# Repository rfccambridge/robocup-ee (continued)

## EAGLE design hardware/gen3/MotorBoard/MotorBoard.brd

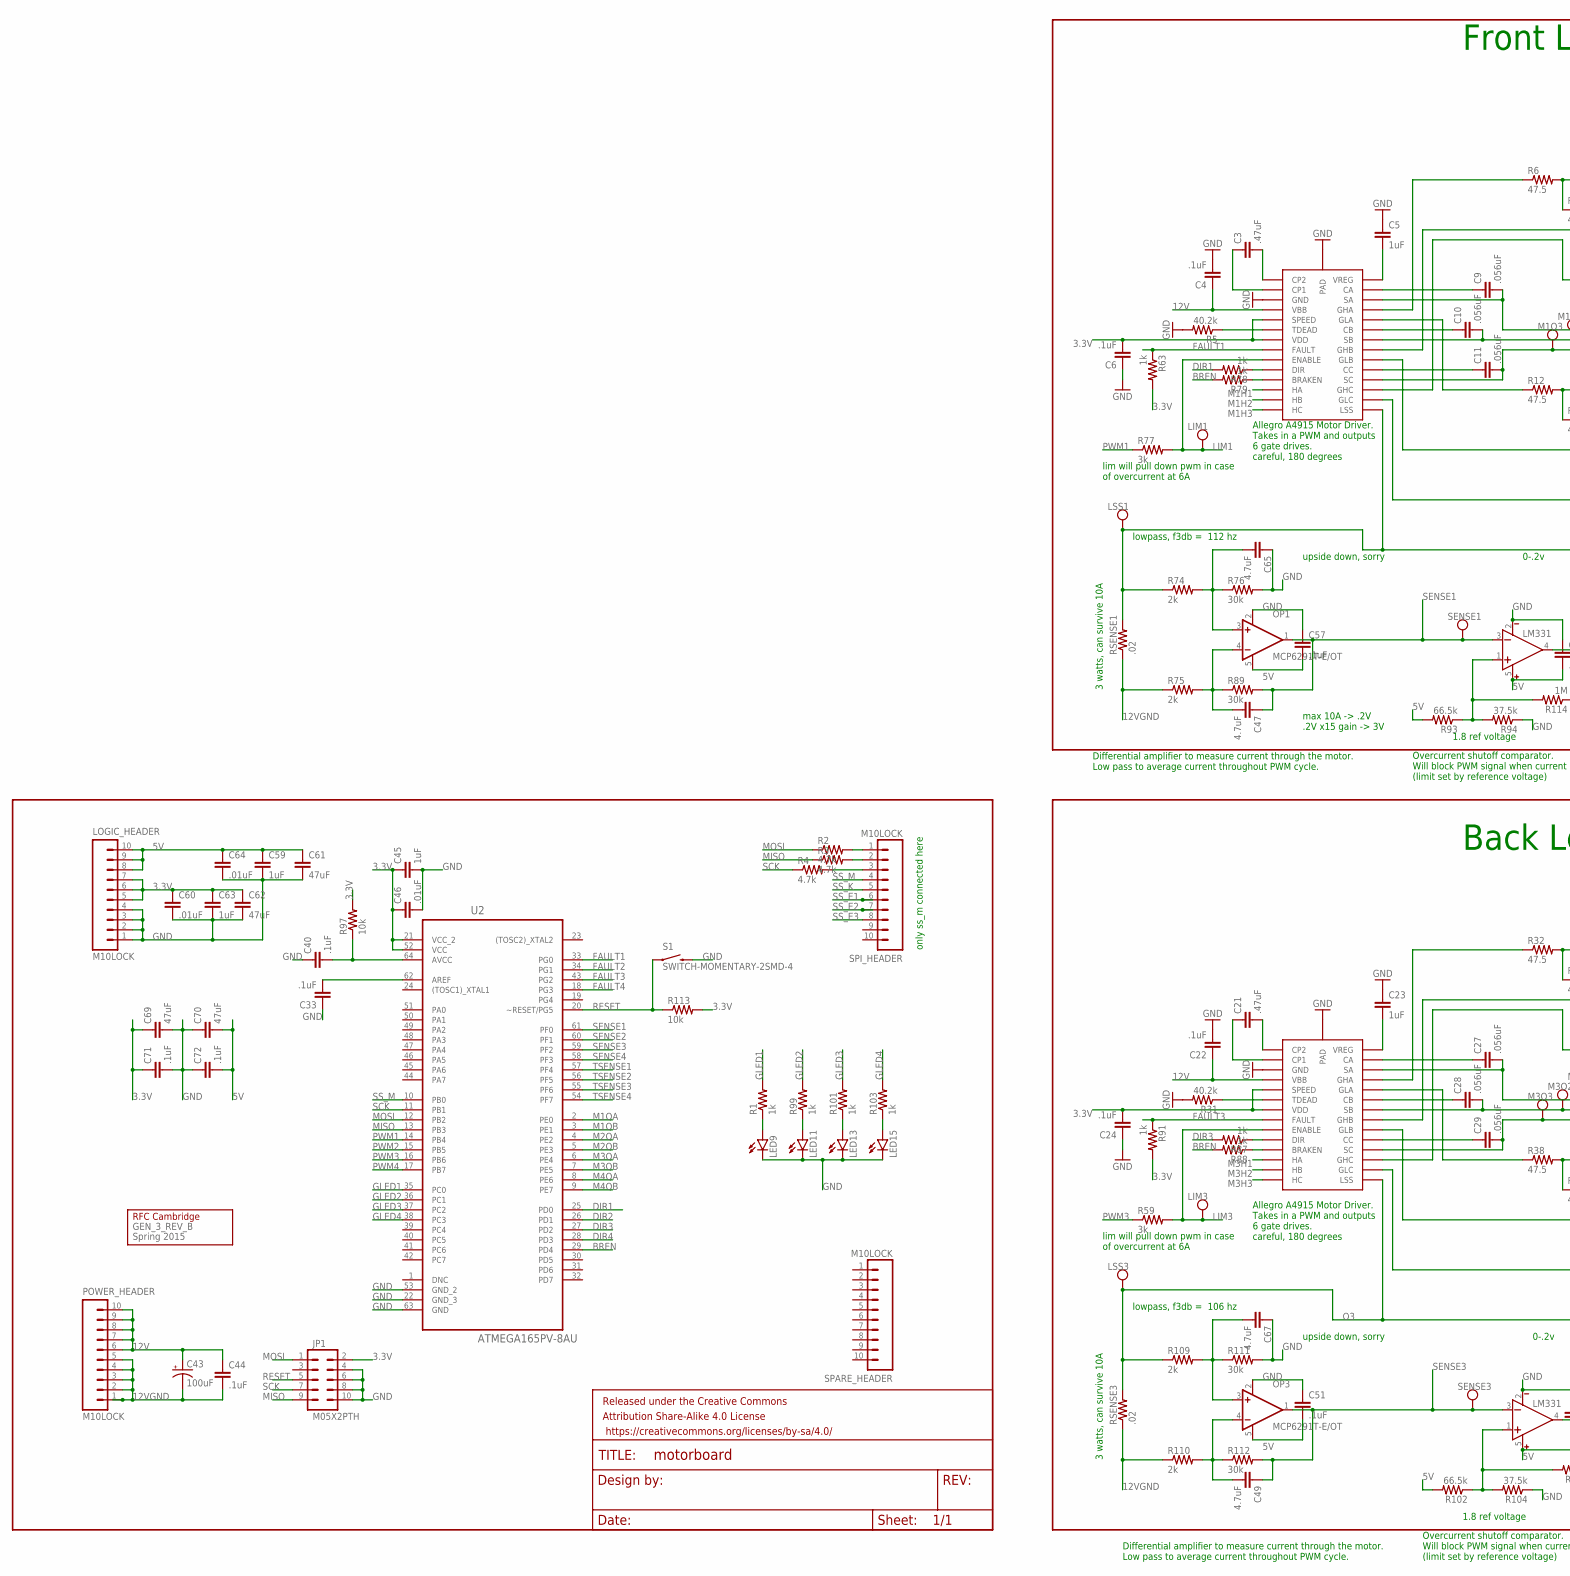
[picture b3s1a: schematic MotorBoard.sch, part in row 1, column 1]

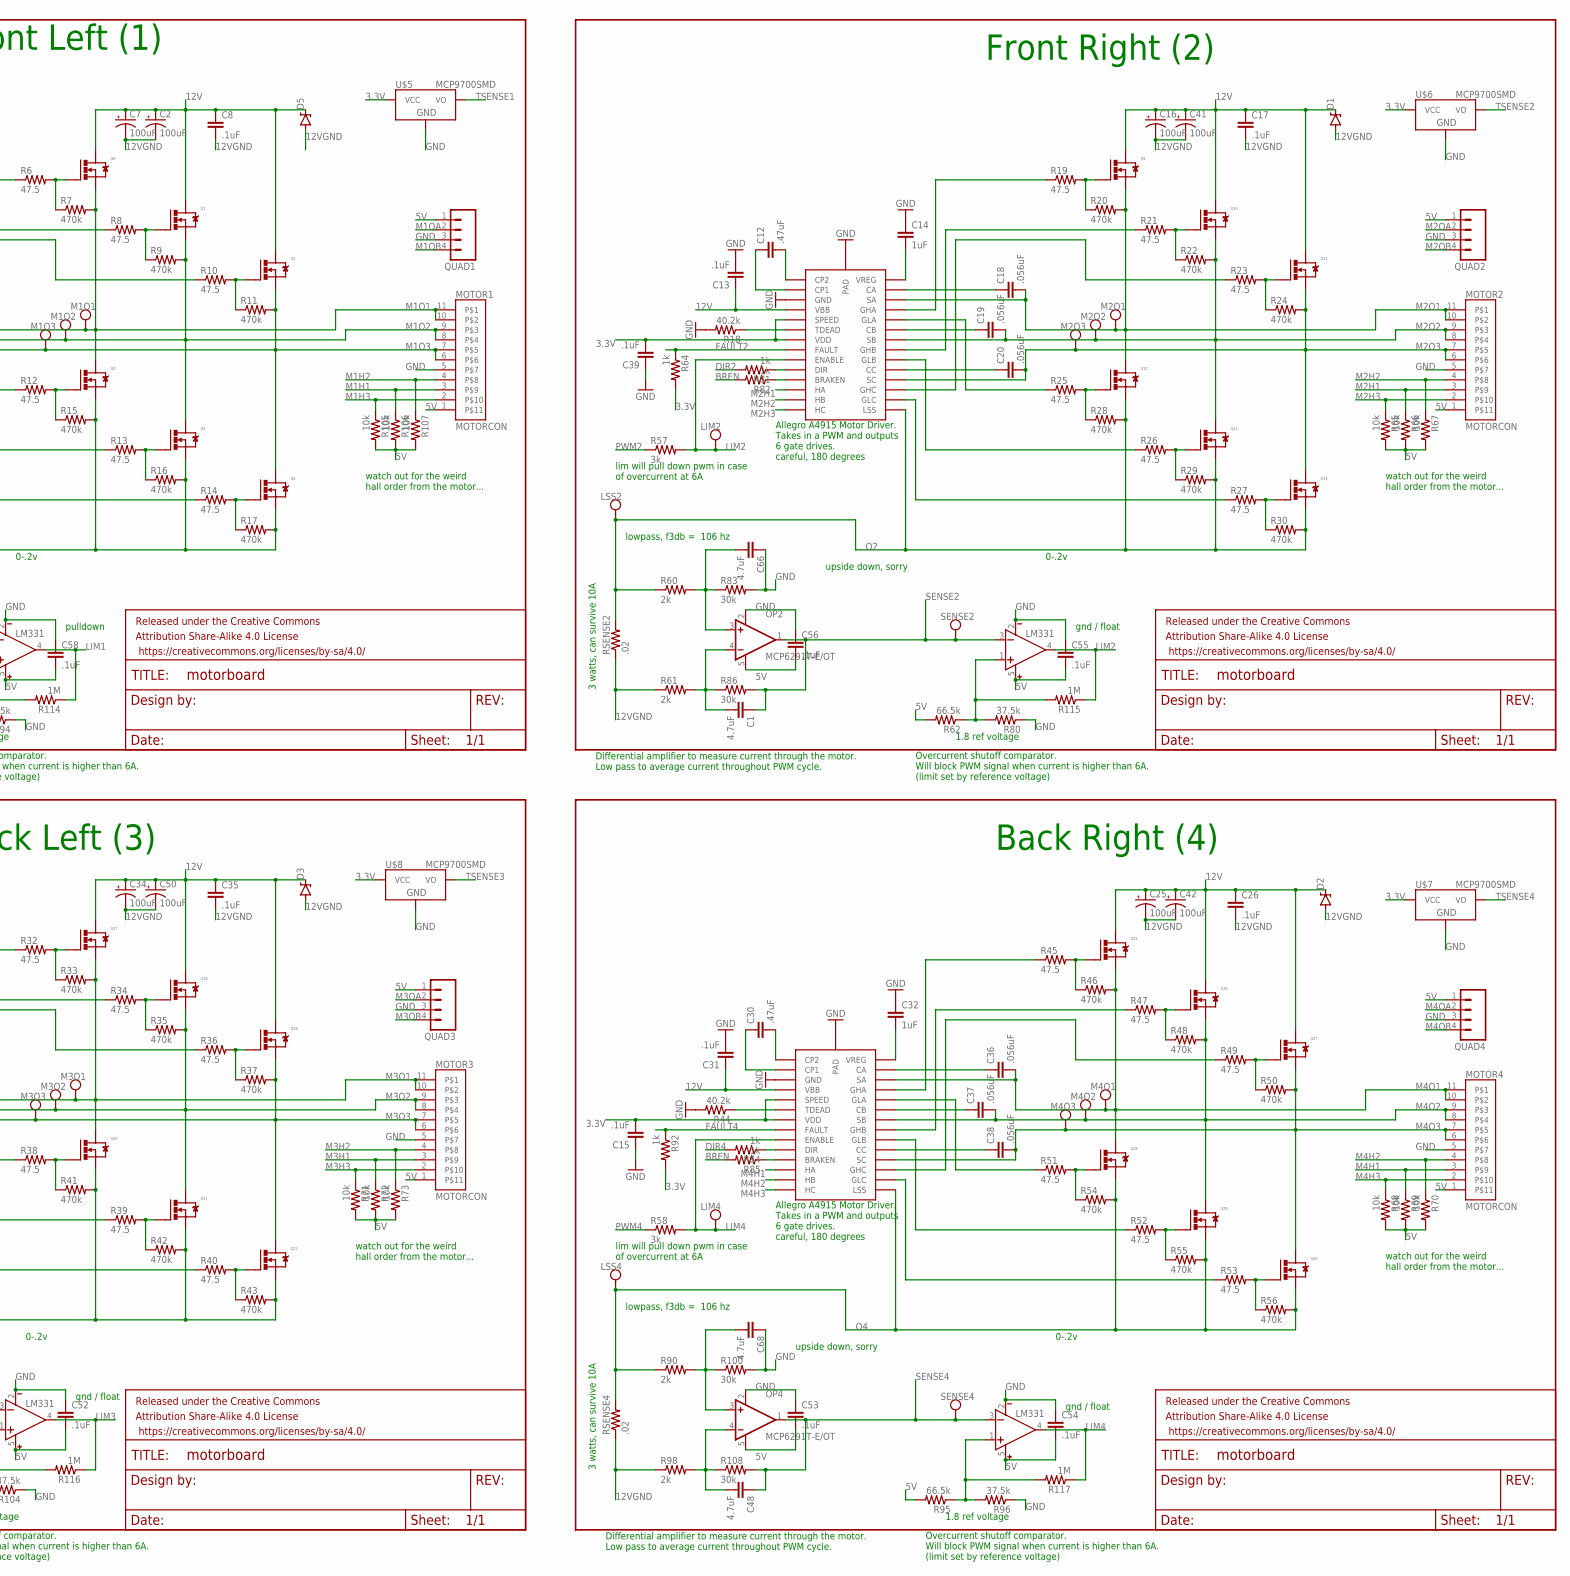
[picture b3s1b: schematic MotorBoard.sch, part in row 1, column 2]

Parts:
C1, C47, C48, C49, C65, C66, C67, C68: 4.7uF; 0805
C2, C7, C16, C25, C34, C41, C42, C43, C50: 100uF; PANASONIC_D
C3, C12, C21, C30: .47uF; 0805
C4, C6, C8, C13, C15, C17, C22, C24, C26, C31, C33, C35, C39, C40, C44, C51, C52, C53, C54, C55, C56, C57, C58, C71, C72: .1uF; 0805
C5, C14, C23, C32, C45, C59, C63: 1uF; 0805
C9, C10, C11, C18, C19, C20, C27, C28, C29, C36, C37, C38: .056uF; 0805
C46, C60, C64: .01uF; 0805
C61, C62, C69, C70: 47uF; 1206
COMP1, COMP2, COMP3, COMP4: LM331; SOT23-5
D1, D2, D3, D5: DIODE-ZENERDO214AC; DO214AC
FRAME1, FRAME2, FRAME5, FRAME6, FRAME7: FRAME-LETTER; CREATIVE_COMMONS
GEN_3_REV_B: Spring 2015; LOGO
JP1: M05X2PTH; AVR_ICSP
LED9, LED11, LED13, LED15: LED1206; LED-1206
LIM1, LIM2, LIM3, LIM4: TEST_PT; TESTING_PT
LOGIC_HEADER: M10LOCK; 1X10_LOCK
LSS1, LSS2, LSS3, LSS4: TEST_PT; TESTING_PT
M1O1, M1O2, M1O3, M2O1, M2O2, M2O3, M3O1, M3O2, M3O3, M4O1, M4O2, M4O3: TEST_PT; TESTING_PT
MOTOR1, MOTOR2, MOTOR3, MOTOR4: MOTORCON; GEN3CON
OP1, OP2, OP3, OP4: MCP6291T-E/OT; SOT23-5
POWER_HEADER: M10LOCK; 1X10_LOCK
Q1, Q2, Q3, Q4, Q5, Q6, Q9, Q10, Q11, Q12, Q13, Q14, Q17, Q18, Q19, Q20, Q21, Q22, Q25, Q26, Q27, Q28, Q29, Q30: N-MOSFET; DPAK
QUAD1, QUAD2, QUAD3, QUAD4: M04LOCK; 1X04_LOCK
R1, R63, R64, R78, R79, R81, R82, R84, R85, R87, R88, R91, R92, R99, R101, R103: 1k; 0805
R2, R3, R4: 4.7k; 0805
R5, R18, R31, R44: 40.2k; 0805
R6, R8, R10, R12, R13, R14, R19, R21, R23, R25, R26, R27, R32, R34, R36, R38, R39, R40, R45, R47, R49, R51, R52, R53: 47.5; 0805
R7, R9, R11, R15, R16, R17, R20, R22, R24, R28, R29, R30, R33, R35, R37, R41, R42, R43, R46, R48, R50, R54, R55, R56: 470k; 0805
R57, R58, R59, R77: 3k; 0805
R60, R61, R74, R75, R90, R98, R109, R110: 2k; 0805
R62, R93, R95, R102: 66.5k; 0805
R65, R66, R67, R68, R69, R70, R71, R72, R73, R97, R105, R106, R107, R113: 10k; 0805
R76, R83, R86, R89, R100, R108, R111, R112: 30k; 0805
R80, R94, R96, R104: 37.5k; 0805
R114, R115, R116, R117: 1M; 0805
RSENSE1, RSENSE2, RSENSE3, RSENSE4: .02; R2512
S1: SWITCH-MOMENTARY-2SMD-4; TACTILE_SWITCH_TALL
SENSE1, SENSE2, SENSE3, SENSE4: TEST_PT; TESTING_PT
SPARE_HEADER: M10LOCK; 1X10_LOCK
SPI_HEADER: M10LOCK; 1X10_LOCK
U2: ATMEGA165PV-8AU; QFP80P1600X1600X120-64N
U$1, U$2, U$3, U$4: A4915; TSSOP28-GROUNDPAD
U$5, U$6, U$7, U$8: MCP9700SMD; SOT23-3

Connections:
3.3V: C6.2, C15.2, C24.2, C39.2, C45.1, C46.1, C60.1, C62.1, C63.1, C69.1, C71.1, JP1.2, LOGIC_HEADER.5, LOGIC_HEADER.6, LOGIC_HEADER.7, R63.2, R64.2, R91.2, R92.2, R97.2, R113.2, U2.21 (VCC_2), U2.52 (VCC), U$1.SPEED, U$1.VDD, U$2.SPEED, U$2.VDD, U$3.SPEED, U$3.VDD, U$4.SPEED, U$4.VDD, U$5.1 (VCC), U$6.1 (VCC), U$7.1 (VCC), U$8.1 (VCC)
5V: C51.2, C52.2, C53.2, C54.2, C55.2, C56.2, C57.2, C58.2, C59.1, C61.1, C64.1, C70.2, C72.2, COMP1.5 (V+), COMP2.5 (V+), COMP3.5 (V+), COMP4.5 (V+), LOGIC_HEADER.8, LOGIC_HEADER.9, LOGIC_HEADER.10, MOTOR1.1, MOTOR2.1, MOTOR3.1, MOTOR4.1, OP1.5 (V+), OP2.5 (V+), OP3.5 (V+), OP4.5 (V+), QUAD1.1, QUAD2.1, QUAD3.1, QUAD4.1, R62.2, R65.2, R66.2, R67.2, R68.2, R69.2, R70.2, R71.2, R72.2, R73.2, R93.2, R95.2, R102.2, R105.2, R106.2, R107.2
12V: C2.+, C4.1, C7.+, C8.1, C13.1, C16.+, C17.1, C22.1, C25.+, C26.1, C31.1, C34.+, C35.1, C41.+, C42.+, C43.+, C44.1, C50.+, D1.C, D2.C, D3.C, D5.C, POWER_HEADER.6, POWER_HEADER.7, POWER_HEADER.8, POWER_HEADER.9, POWER_HEADER.10, Q1.DRAIN, Q2.DRAIN, Q6.DRAIN, Q9.DRAIN, Q10.DRAIN, Q11.DRAIN, Q17.DRAIN, Q18.DRAIN, Q19.DRAIN, Q25.DRAIN, Q26.DRAIN, Q27.DRAIN, U$1.VBB, U$2.VBB, U$3.VBB, U$4.VBB
12VGND: C2.-, C7.-, C8.2, C16.-, C17.2, C25.-, C26.2, C34.-, C35.2, C41.-, C42.-, C43.-, C44.2, C50.-, D1.A, D2.A, D3.A, D5.A, POWER_HEADER.1, POWER_HEADER.2, POWER_HEADER.3, POWER_HEADER.4, POWER_HEADER.5, R61.1, R75.1, R98.1, R110.1, RSENSE1.1, RSENSE2.1, RSENSE3.1, RSENSE4.1
AREF: C33.2, U2.62 (AREF)
AVCC: C40.2, R97.1, U2.64 (AVCC)
BREN: R79.2, R82.2, R85.2, R88.2, U2.29 (PD4)
CP1: C3.1, U$4.CP1
CP2: C3.2, U$4.CP2
DIR1: R78.2, U2.25 (PD0)
DIR2: R81.2, U2.26 (PD1)
DIR3: R87.2, U2.27 (PD2)
DIR4: R84.2, U2.28 (PD3)
FAULT1: R63.1, U2.33 (PG0), U$4.FAULT
FAULT2: R64.1, U2.34 (PG1), U$1.FAULT
FAULT3: R91.1, U2.43 (PG2), U$2.FAULT
FAULT4: R92.1, U2.18 (PG3), U$3.FAULT
GLED1: R1.2, U2.35 (PC0)
GLED2: R99.2, U2.36 (PC1)
GLED3: R101.2, U2.37 (PC2)
GLED4: R103.2, U2.38 (PC3)
GND: C4.2, C5.1, C6.1, C13.2, C14.1, C15.1, C22.2, C23.1, C24.1, C31.2, C32.1, C33.1, C39.1, C40.1, C45.2, C46.2, C51.1, C52.1, C53.1, C54.1, C55.1, C56.1, C57.1, C58.1, C59.2, C60.2, C61.2, C62.2, C63.2, C64.2, C65.1, C66.1, C67.1, C68.1, C69.2, C70.1, C71.2, C72.1, COMP1.2 (V-), COMP2.2 (V-), COMP3.2 (V-), COMP4.2 (V-), JP1.4, JP1.6, JP1.8, JP1.10, LED9.C, LED11.C, LED13.C, LED15.C, LOGIC_HEADER.1, LOGIC_HEADER.2, LOGIC_HEADER.3, LOGIC_HEADER.4, MOTOR1.5, MOTOR2.5, MOTOR3.5, MOTOR4.5, OP1.2 (V-), OP2.2 (V-), OP3.2 (V-), OP4.2 (V-), QUAD1.3, QUAD2.3, QUAD3.3, QUAD4.3, R5.2, R18.2, R31.2, R44.2, R76.2, R80.1, R83.2, R94.1, R96.1, R100.2, R104.1, R111.2, S1.B2 (2), U2.22 (GND_3), U2.53 (GND_2), U2.63 (GND), U$1.GND, U$1.PAD, U$2.GND, U$2.PAD, U$3.GND, U$3.PAD, U$4.GND, U$4.PAD, U$5.3 (GND), U$6.3 (GND), U$7.3 (GND), U$8.3 (GND)
LIM1: COMP1.4 (OUT), LIM1.P$1, R77.2, R114.1, U$4.ENABLE
LIM2: COMP2.4 (OUT), LIM2.P$1, R57.2, R115.1, U$1.ENABLE
LIM3: COMP3.4 (OUT), LIM3.P$1, R59.2, R116.1, U$2.ENABLE
LIM4: COMP4.4 (OUT), LIM4.P$1, R58.2, R117.1, U$3.ENABLE
M1H1: MOTOR1.3, R106.1, U$4.HA
M1H2: MOTOR1.4, R107.1, U$4.HB
M1H3: MOTOR1.2, R105.1, U$4.HC
M1O1: C9.2, M1O1.P$1, MOTOR1.10, MOTOR1.11, Q3.DRAIN, Q6.SOURCE, R7.2, U$4.SA
M1O2: C10.2, M1O2.P$1, MOTOR1.8, MOTOR1.9, Q1.SOURCE, Q4.DRAIN, R9.2, U$4.SB
M1O3: C11.2, M1O3.P$1, MOTOR1.6, MOTOR1.7, Q2.SOURCE, Q5.DRAIN, R11.2, U$4.SC
M1QA: QUAD1.2, U2.2 (PE0)
M1QB: QUAD1.4, U2.3 (PE1)
M2H1: MOTOR2.3, R66.1, U$1.HA
M2H2: MOTOR2.4, R67.1, U$1.HB
M2H3: MOTOR2.2, R65.1, U$1.HC
M2O1: C18.2, M2O1.P$1, MOTOR2.10, MOTOR2.11, Q9.SOURCE, Q12.DRAIN, R20.2, U$1.SA
M2O2: C19.2, M2O2.P$1, MOTOR2.8, MOTOR2.9, Q10.SOURCE, Q13.DRAIN, R22.2, U$1.SB
M2O3: C20.2, M2O3.P$1, MOTOR2.6, MOTOR2.7, Q11.SOURCE, Q14.DRAIN, R24.2, U$1.SC
M2QA: QUAD2.2, U2.4 (PE2)
M2QB: QUAD2.4, U2.5 (PE3)
M3H1: MOTOR3.3, R72.1, U$2.HA
M3H2: MOTOR3.4, R73.1, U$2.HB
M3H3: MOTOR3.2, R71.1, U$2.HC
M3O1: C27.2, M3O1.P$1, MOTOR3.10, MOTOR3.11, Q17.SOURCE, Q20.DRAIN, R33.2, U$2.SA
M3O2: C28.2, M3O2.P$1, MOTOR3.8, MOTOR3.9, Q18.SOURCE, Q21.DRAIN, R35.2, U$2.SB
M3O3: C29.2, M3O3.P$1, MOTOR3.6, MOTOR3.7, Q19.SOURCE, Q22.DRAIN, R37.2, U$2.SC
M3QA: QUAD3.2, U2.6 (PE4)
M3QB: QUAD3.4, U2.7 (PE5)
M4H1: MOTOR4.3, R69.1, U$3.HA
M4H2: MOTOR4.4, R70.1, U$3.HB
M4H3: MOTOR4.2, R68.1, U$3.HC
M4O1: C36.2, M4O1.P$1, MOTOR4.10, MOTOR4.11, Q25.SOURCE, Q28.DRAIN, R46.2, U$3.SA
M4O2: C37.2, M4O2.P$1, MOTOR4.8, MOTOR4.9, Q26.SOURCE, Q29.DRAIN, R48.2, U$3.SB
M4O3: C38.2, M4O3.P$1, MOTOR4.6, MOTOR4.7, Q27.SOURCE, Q30.DRAIN, R50.2, U$3.SC
M4QA: QUAD4.2, U2.8 (PE6)
M4QB: QUAD4.4, U2.9 (PE7)
MISO: JP1.9, R3.1, U2.13 (PB3)
MOSI: JP1.1, R2.1, U2.12 (PB2)
unnamed: LED9.A, R1.1
unnamed: C66.2, OP2.3 (+IN), R60.2, R83.1
unnamed: R3.2, SPI_HEADER.2
unnamed: R4.2, SPI_HEADER.3
unnamed: C5.2, U$4.VREG
unnamed: Q6.GATE, R6.2, R7.1
unnamed: Q1.GATE, R8.2, R9.1
unnamed: Q2.GATE, R10.2, R11.1
unnamed: Q3.GATE, R12.2, R15.1
unnamed: Q4.GATE, R13.2, R16.1
unnamed: Q5.GATE, R14.2, R17.1
unnamed: C1.2, OP2.4 (-IN), R61.2, R86.1
unnamed: R6.1, U$4.GHA
unnamed: R14.1, U$4.GLC
unnamed: R13.1, U$4.GLB
unnamed: R12.1, U$4.GLA
unnamed: R8.1, U$4.GHB
unnamed: R10.1, U$4.GHC
unnamed: COMP2.1 (IN+), R62.1, R80.2, R115.2
unnamed: C12.1, U$1.CP1
unnamed: C11.1, U$4.CC
unnamed: C12.2, U$1.CP2
unnamed: R18.1, U$1.TDEAD
unnamed: C20.1, U$1.CC
unnamed: C10.1, U$4.CB
unnamed: C19.1, U$1.CB
unnamed: C18.1, U$1.CA
unnamed: C14.2, U$1.VREG
unnamed: C9.1, U$4.CA
unnamed: Q9.GATE, R19.2, R20.1
unnamed: Q10.GATE, R21.2, R22.1
unnamed: Q11.GATE, R23.2, R24.1
unnamed: Q12.GATE, R25.2, R28.1
unnamed: Q13.GATE, R26.2, R29.1
unnamed: Q14.GATE, R27.2, R30.1
unnamed: R19.1, U$1.GHA
unnamed: R27.1, U$1.GLC
unnamed: R26.1, U$1.GLB
unnamed: R25.1, U$1.GLA
unnamed: R21.1, U$1.GHB
unnamed: R23.1, U$1.GHC
unnamed: R2.2, SPI_HEADER.1
unnamed: C65.2, OP1.3 (+IN), R74.2, R76.1
unnamed: C21.1, U$2.CP1
unnamed: C21.2, U$2.CP2
unnamed: R31.1, U$2.TDEAD
unnamed: C29.1, U$2.CC
unnamed: C28.1, U$2.CB
unnamed: C27.1, U$2.CA
unnamed: C23.2, U$2.VREG
unnamed: Q17.GATE, R32.2, R33.1
unnamed: Q18.GATE, R34.2, R35.1
unnamed: Q19.GATE, R36.2, R37.1
unnamed: Q20.GATE, R38.2, R41.1
unnamed: Q21.GATE, R39.2, R42.1
unnamed: Q22.GATE, R40.2, R43.1
unnamed: R32.1, U$2.GHA
unnamed: R40.1, U$2.GLC
unnamed: R39.1, U$2.GLB
unnamed: R38.1, U$2.GLA
unnamed: R34.1, U$2.GHB
unnamed: R36.1, U$2.GHC
unnamed: COMP1.1 (IN+), R93.1, R94.2, R114.2
unnamed: C68.2, OP4.3 (+IN), R90.2, R100.1
unnamed: C30.1, U$3.CP1
unnamed: C30.2, U$3.CP2
unnamed: R44.1, U$3.TDEAD
unnamed: C38.1, U$3.CC
unnamed: C37.1, U$3.CB
unnamed: C36.1, U$3.CA
unnamed: C32.2, U$3.VREG
unnamed: Q25.GATE, R45.2, R46.1
unnamed: Q26.GATE, R47.2, R48.1
unnamed: Q27.GATE, R49.2, R50.1
unnamed: Q28.GATE, R51.2, R54.1
unnamed: Q29.GATE, R52.2, R55.1
unnamed: Q30.GATE, R53.2, R56.1
unnamed: R45.1, U$3.GHA
unnamed: R53.1, U$3.GLC
unnamed: R52.1, U$3.GLB
unnamed: R51.1, U$3.GLA
unnamed: R47.1, U$3.GHB
unnamed: R49.1, U$3.GHC
unnamed: C48.2, OP4.4 (-IN), R98.2, R108.1
unnamed: COMP4.1 (IN+), R95.1, R96.2, R117.2
unnamed: C67.2, OP3.3 (+IN), R109.2, R111.1
unnamed: C49.2, OP3.4 (-IN), R110.2, R112.1
unnamed: COMP3.1 (IN+), R102.1, R104.2, R116.2
unnamed: C47.2, OP1.4 (-IN), R75.2, R89.1
unnamed: R78.1, U$4.DIR
unnamed: R79.1, U$4.BRAKEN
unnamed: R81.1, U$1.DIR
unnamed: R82.1, U$1.BRAKEN
unnamed: R84.1, U$3.DIR
unnamed: R85.1, U$3.BRAKEN
unnamed: R88.1, U$2.BRAKEN
unnamed: R87.1, U$2.DIR
unnamed: LED11.A, R99.1
unnamed: LED13.A, R101.1
unnamed: LED15.A, R103.1
O1: LSS1.P$1, Q3.SOURCE, Q4.SOURCE, Q5.SOURCE, R15.2, R16.2, R17.2, R74.1, RSENSE1.2, U$4.LSS
O2: LSS2.P$1, Q12.SOURCE, Q13.SOURCE, Q14.SOURCE, R28.2, R29.2, R30.2, R60.1, RSENSE2.2, U$1.LSS
O3: LSS3.P$1, Q20.SOURCE, Q21.SOURCE, Q22.SOURCE, R41.2, R42.2, R43.2, R109.1, RSENSE3.2, U$2.LSS
O4: LSS4.P$1, Q28.SOURCE, Q29.SOURCE, Q30.SOURCE, R54.2, R55.2, R56.2, R90.1, RSENSE4.2, U$3.LSS
PWM1: R77.1, U2.14 (PB4)
PWM2: R57.1, U2.15 (PB5)
PWM3: R59.1, U2.16 (PB6)
PWM4: R58.1, U2.17 (PB7)
RESET: JP1.5, R113.1, S1.A2 (1), U2.20 (~RESET/PG5)
SCK: JP1.7, R4.1, U2.11 (PB1)
SENSE1: C47.1, COMP1.3 (IN-), OP1.1 (OUT), R89.2, SENSE1.P$1, U2.61 (PF0)
SENSE2: C1.1, COMP2.3 (IN-), OP2.1 (OUT), R86.2, SENSE2.P$1, U2.60 (PF1)
SENSE3: C49.1, COMP3.3 (IN-), OP3.1 (OUT), R112.2, SENSE3.P$1, U2.59 (PF2)
SENSE4: C48.1, COMP4.3 (IN-), OP4.1 (OUT), R108.2, SENSE4.P$1, U2.58 (PF3)
SS_E1: SPI_HEADER.6
SS_E2: SPI_HEADER.7
SS_E3: SPI_HEADER.8
SS_K: SPI_HEADER.5
SS_M: SPI_HEADER.4, U2.10 (PB0)
TDEAD: R5.1, U$4.TDEAD
TSENSE1: U2.57 (PF4), U$5.2 (VO)
TSENSE2: U2.56 (PF5), U$6.2 (VO)
TSENSE3: U2.55 (PF6), U$8.2 (VO)
TSENSE4: U2.54 (PF7), U$7.2 (VO)

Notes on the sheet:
Front Left (1)
Front Right (2)
Back Right (4)
Back Left (3)
Allegro A4915 Motor Driver. Takes in a PWM and outputs 6 gate drives. careful, 180 degrees
0-.2v
max 10A -> .2V .2V x15 gain -> 3V
3 watts, can survive 10A
upside down, sorry
only ss_m connected here
lowpass, f3db = 112 hz
1.8 ref voltage
pulldown
lim will pull down pwm in case of overcurrent at 6A
gnd / float
lowpass, f3db = 106 hz
watch out for the weird hall order from the motor...
Differential amplifier to measure current through the motor. Low pass to average current throughout PWM cycle.
Overcurrent shutoff comparator. Will block PWM signal when current is higher than 6A. (limit set by reference voltage)

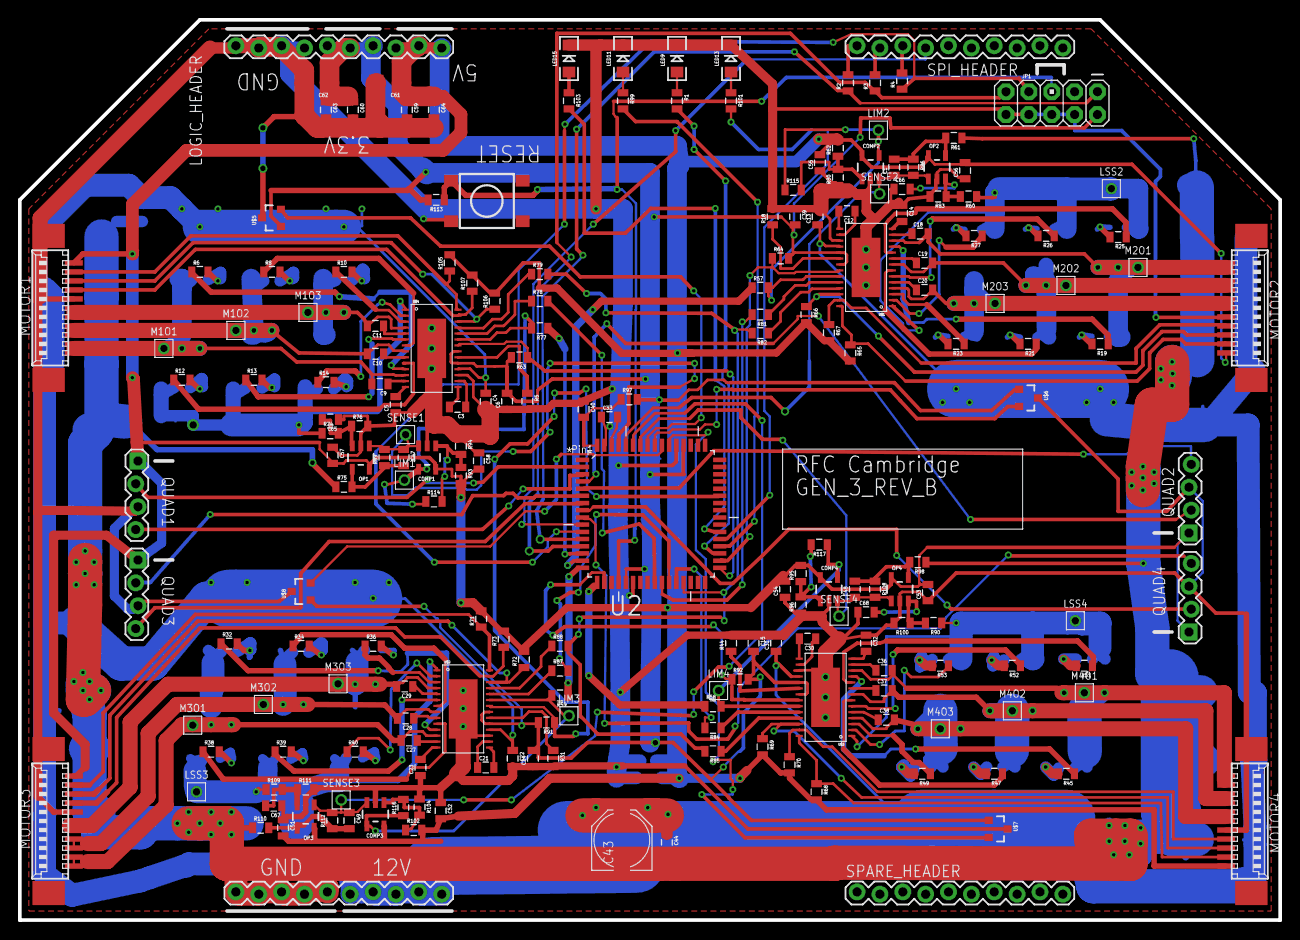
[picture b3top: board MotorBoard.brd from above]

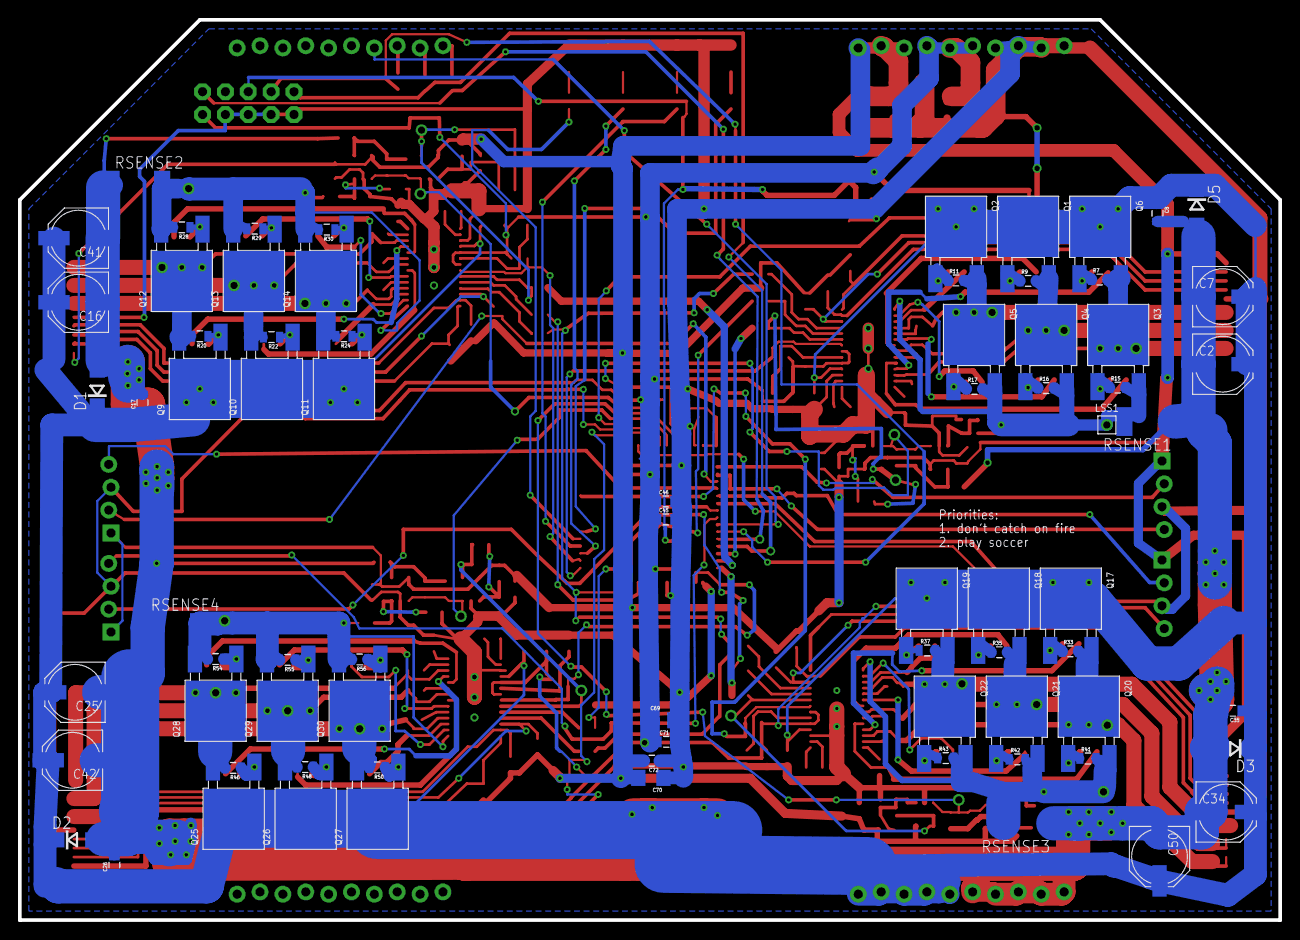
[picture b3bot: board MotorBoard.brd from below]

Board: 2 copper layers, 140.0 x 100.0 mm, 286 parts (76 on the bottom side), 180 nets.
